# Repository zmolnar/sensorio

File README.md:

# The story of sensorio: a "smart" variometer

Since I left the university, I always wanted to gain a deeper understanding of how Kalman filters work in practice. I started to do research on the topic, until I found an excellent paper from [Roger Labbe](https://github.com/rlabbe/Kalman-and-Bayesian-Filters-in-Python), describing the Bayesian filters in great detail and in a very practical way.

After reading the book, I wanted to implement it in a real-life project. Since I'm a passionate paraglider pilot, building a variometer was a straightforward direction for me.

A variometer is a flight instrument, measuring vertical height and velocity, based on barometric pressure. Since pressure measurement is very noisy, in most cases (even in commercial products), a low pass filter is used to smoothen it, resulting in many seconds of lag in the output. This is how it has always been and this is something that every pilot has to learn how to compensate mentally, using prior experience and listening to other sources of information, like feeling of acceleration. It can be very hard to learn and master especially for beginners. To solve this, many people have already built variometers combining a pressure sensor and an accelerometer, with promising results.

I started to design the hardware, but I hit walls right at the beginning. The STM32 micros, that I have a lot of experience with, are not available due to global chip shortage, so I had to find an alternative. I choose ESP32, because it has lots of computing power, it is on stock and has additional built-in capabilities - like Bluetooth and WiFi - providing great potential for future developments.

The other crucial part of the project was to find the appropriate display. The special flying conditions require very good readability under any circumstances, therefore I choose the [LS027B7DH01](https://www.sharpsde.com/products/displays/model/ls027b7dh01/), a transflective LCD from Sharp, which I ordered from [Digikey](https://www.digikey.com/en/products/detail/sharp-microelectronics/LS027B7DH01/5054066).

I used KiCad for PCB design and FreeCAD for the housing. You can find the project files in the hardware and housing folders.

While waiting for the PCB, I started to experiment with Arduino, but I had to realize quickly that it is not suitable for me. I changed to ESP IDF and it was a very good decision. I am satisfied with the framework, it has lots of documentation, clear examples, a well designed interface, and works out of the box.

My first task was to fire up the sensors on the board, still using development kits:
+ [MS5611](https://www.amsys-sensor.com/products/pressure-sensor/ms5611-high-resolution-barometric-sensor-10-1200-mbar/) pressure sensor: I know this sensor very well, it was an easy task to make it work. I connected it to the ESP32 using I2C
+ [LS027B7DH01](https://www.sharpsde.com/products/displays/model/ls027b7dh01/): I used SPI to connect it to the MCU. I use the LVGL graphics library to implement the UI
+ [BNO055](https://www.bosch-sensortec.com/products/smart-sensors/bno055/) IMU from Bosch, who provides the needed driver too

The MS5611 and the LCD were very easy, but I struggled with the IMU. Everything worked fine for some time, but after a few seconds or sometimes minutes, the communication stopped and only a power reset could solve the problem. A friend of mine lent me a [Saleae](https://www.saleae.com/) Logic Pro 16, to investigate the issue, and I quickly found the root cause: the I2C clock stretching is not handled properly in the driver. After I added a timeout to mimic clock stretching, the issue disappeared and now the IMU works perfectly. The main issue was that BNO055 has a complex internal algorithm that takes some time to run, therefore it stretches the clock cycle until it finishes the task. The communication worked as long as the internal sensors were not ready, but after it had calibrated the system and started the algorithm, the communication stopped. I could have struggled a lot without a logic analyzer, because working with hardware without having a logic analyzer at hand is like solving a rubik's cube in a dark room without any visual feedback. Until each bit is in its exact position at the right time, the program does not work and it is very hard to find the root cause just by reading the code.
I was amazed by the build quality of the Saleae device. It is very simple to use, although I found it annoying that the labels numbering the input channels are placed on the backplane of the housing. Other than that, it is clearly a professional tool made for heavy duty embedded development. The software is simple to install and straightforward to use even without reading the manual, because it is really intuitive. I also experimented with an SD card and Saleae logic analyzer to discover the potential of the device. It looks really cool!

SD card setup

Wiring

Decoded SPI frame

Decoded SPI byte

400kHz SPI clock signal

After making the board up and running, I sampled input data using real sensors, and started to experiment with Kalman filters. First, I designed an unscented kalman filter (UKF) using filterpy. I was truly satisfied by the results and started to work on my own implementation in C++.

Although the results were very promising at first sight, I encountered problems. I had to realize that the IMU has an orientation-dependent, constantly changing offset that introduces an unacceptable error in the final result. This offset is accumulated only in a standstill position and is eliminated internally when the device is moving, but it’s a bit annoying while waiting for take off.

The other, show stopper issue is that BNO055 is not suitable for this task. Since only the vertical acceleration is relevant for the computation, detecting the direction of the gravity vector is a crucial step. BNO055 fails to detect the vertical direction if the device is in a constantly accelerating situation and it provides false results. This happens when flying in a narrow thermal, resulting in a constantly beeping variometer indicating crazy climb rates, even though the vertical speed is minimal. This is totally unacceptable and I’m very disappointed. I didn’t recognize this problem early enough when selecting the accelerometer, although even the documentation does not emphasise it either. Only a small note states this behavior, which is very frustrating. Lessons learned ...

Considering the results, I decided to build a new device using 4 baro sensors and no IMU. This way I can increase the sampling rate and make the device more responsive to changes without the problems introduced by accelerometers. I could also try [Madgwick's](https://x-io.co.uk/open-source-imu-and-ahrs-algorithms/) algorithm, but I decided to go in this direction first.

This project is still in concept phase, it requires a lot of work to finish it. Until then watch these videos and stay tuned!

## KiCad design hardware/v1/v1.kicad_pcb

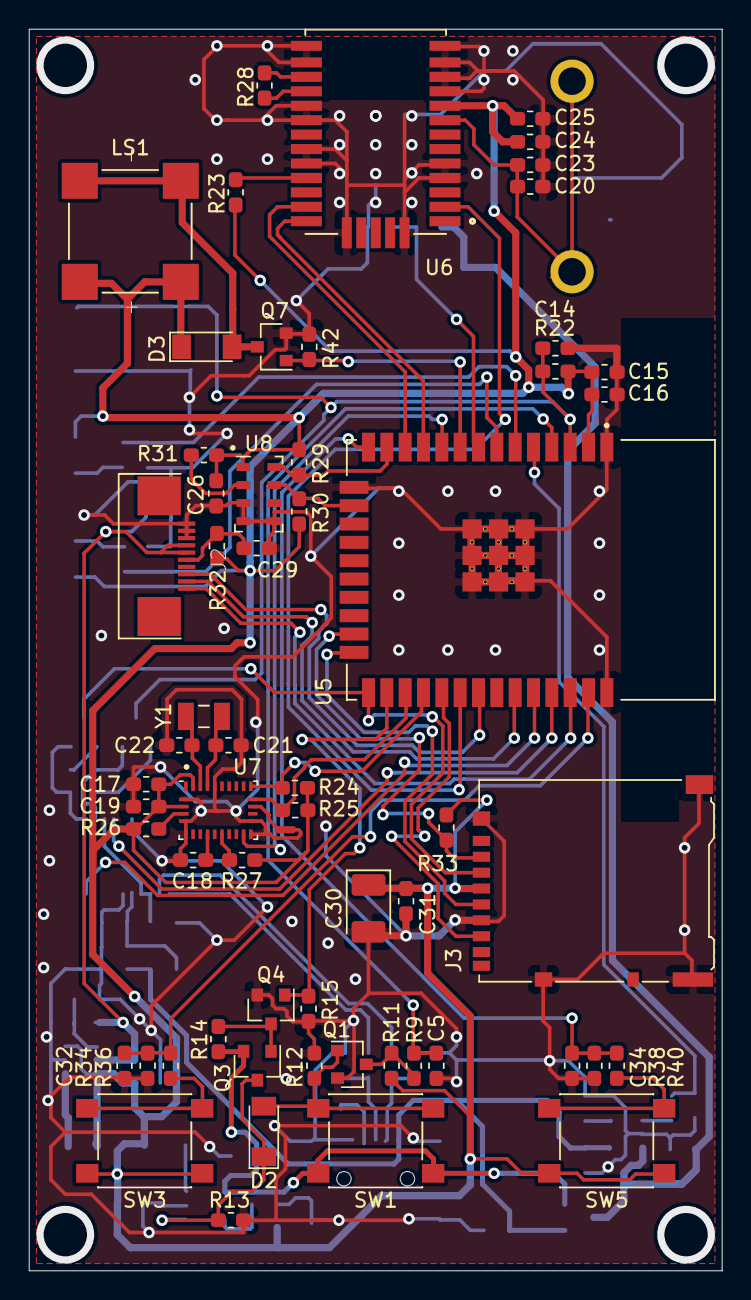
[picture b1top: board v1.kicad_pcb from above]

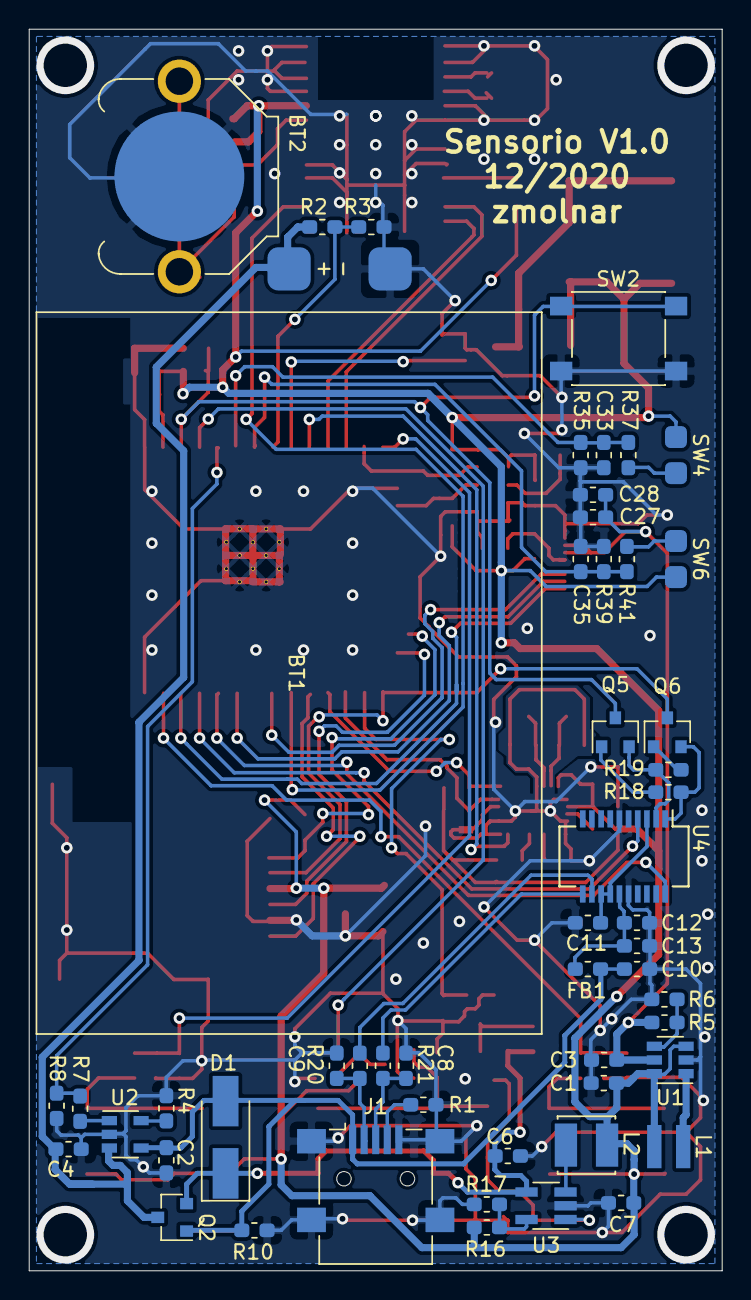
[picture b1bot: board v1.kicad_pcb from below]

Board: 2 copper layers, 48.0 x 86.0 mm, 112 parts (52 on the bottom side), 71 nets.

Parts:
BT1: Li-Po, 3,7V; Battery_103450
BT2: CR1220; BatteryHolder_Keystone_3001_1x12mm
C1, C23: 4u7; C_0603_1608Metric_Pad1.05x0.95mm_HandSolder
C2, C4, C6, C13: 4.7u; C_0603_1608Metric_Pad1.05x0.95mm_HandSolder
C3, C7, C24: 10u; C_0603_1608Metric_Pad1.05x0.95mm_HandSolder
C5, C32, C33, C34, C35: 10n; C_0603_1608Metric_Pad1.05x0.95mm_HandSolder
C8, C9: 47p; C_0603_1608Metric_Pad1.05x0.95mm_HandSolder
C10, C11, C12, C14, C16, C19, C20, C25, C26, C29, C31: 100n; C_0603_1608Metric_Pad1.05x0.95mm_HandSolder
C15: 22u; C_0603_1608Metric_Pad1.05x0.95mm_HandSolder
C17: 150n; C_0603_1608Metric_Pad1.05x0.95mm_HandSolder
C18, C27, C28: 1u; C_0603_1608Metric_Pad1.05x0.95mm_HandSolder
C21, C22: 12p; C_0603_1608Metric_Pad1.05x0.95mm_HandSolder
C30: 47u; CP_EIA-3528-21_Kemet-B_Pad1.50x2.35mm_HandSolder
D1: SK24A; D_SMA_Handsoldering
D2, D3: LL46; D_MiniMELF
FB1: Ferrite_Bead; L_0603_1608Metric_Pad1.05x0.95mm_HandSolder
J1: USB_B_Mini; USB_Mini-B_Lumberg_2486_01_Horizontal
J2: Conn_01x10; Wuerth_10pin_FPC_68711014022
J3: Micro_SD_Card_Det; microSD_HC_Hirose_DM3AT-SF-PEJM5
L1: 4u7; Viking_Tech_SDIA0315
L2: 2.2uH; Murata_2u2H_LQH44PN2R2MP0L
LS1: KSSGJ4D20
NT1: GND-to-COM2; NetTie-2_SMD_Pad0.5mm
Q1, Q4, Q7: 2N7002; SOT-23
Q2: DMG2301L; SOT-23
Q3: FDV304P; SOT-23
Q5, Q6: BC817; SOT-23
R1, R10, R11, R12, R13, R14, R15: 100k; R_0603_1608Metric_Pad1.05x0.95mm_HandSolder
R2, R6, R8: 220k; R_0603_1608Metric_Pad1.05x0.95mm_HandSolder
R3, R5: 680k; R_0603_1608Metric_Pad1.05x0.95mm_HandSolder
R4: 2k; R_0603_1608Metric_Pad1.05x0.95mm_HandSolder
R7: 110k; R_0603_1608Metric_Pad1.05x0.95mm_HandSolder
R9, R36, R37, R40, R41: 1k; R_0603_1608Metric_Pad1.05x0.95mm_HandSolder
R16: 680; R_0603_1608Metric_Pad1.05x0.95mm_HandSolder
R17: 150; R_0603_1608Metric_Pad1.05x0.95mm_HandSolder
R18, R19, R22, R23, R24, R25, R26, R27, R29, R30, R31, R32, R33, R34, R35, R38, R39: 10k; R_0603_1608Metric_Pad1.05x0.95mm_HandSolder
R20, R21: 27R; R_0603_1608Metric_Pad1.05x0.95mm_HandSolder
R28: 0R; R_0603_1608Metric_Pad1.05x0.95mm_HandSolder
R42: 100K; R_0603_1608Metric_Pad1.05x0.95mm_HandSolder
SW1: BT0; SW_SPST_PTS645
SW2: RESET; SW_SPST_PTS645
SW3: BT1; SW_SPST_PTS645
SW4: BT3; Connector_SMD_01x02_2.54
SW5: BT2; SW_SPST_PTS645
SW6: BT4; Connector_SMD_01x02_2.54
U1: MCP1640CH; SOT-23-6
U2: MCP73831-2-OT; SOT-23-5
U3: TLV62565; SOT-23-5_HandSoldering
U4: FT231XS; SSOP-20_3.9x8.7mm_P0.635mm
U5: ESP32-WROOM-32D
U6: Quectel_L96-M33
U7: BNO055; LGA-28_5.2x3.8mm_P0.5mm
U8: MS5611-01BA; LGA-8_3x5mm_P1.25mm
Y1: Crystal; Abracon_ABS07-32.768KHZ-T

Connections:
+3V3: C1.1, C7.1, C15.1, C16.1, C17.2, C19.2, C24.1, C25.1, C26.2, C30.1, C31.1, D3.1, J3.4, L1.1, L2.2, LS1.P1, LS1.P2, R11.1, R16.1, R22.1, R23.1, R24.1, R25.1, R26.1, R27.1, R29.1, R30.1, R31.1, R32.1, R33.1, SW3.2, SW4.2, SW5.2, SW6.2, U1.3, U1.6, U5.2, U6.9, U7.3, U7.28, U8.1
+5V: C3.1, C27.1, C28.1, J2.6, J2.7, R5.1, U1.5
+BATT: BT1.1, C4.1, Q2.3, R2.1, U2.3
BAT-ADC: R2.2, R3.1, U5.8
BAT-STAT: R7.2, R8.1, U5.5
BMP-SCL: R29.2, U5.13, U8.8
BMP-SDA: R30.2, U5.16, U8.7
BNO-INT: U5.10, U7.14
BNO-SCL: R25.2, U5.27, U7.19
BNO-SDA: R24.2, U5.28, U7.20
BT1: C32.1, R34.1, R36.2, U5.37
BT2: C34.1, R38.1, R40.2, U5.14
BT3: C33.1, R35.1, R37.2, U5.6
BT4: C35.1, R39.1, R41.2, U5.7
BUZZER: Q7.1, R42.1, U5.9
DTR: Q6.2, R18.2, U4.1
ESP32-EN: C14.1, Q5.3, R22.2, SW2.2, U5.3
ESP32-IO0: J3.3, Q6.3, U5.25
ESP32-RXD0: U4.20, U5.34
ESP32-TXD0: U4.4, U5.35
GND: BT1.2, BT2.2, C1.2, C2.2, C3.2, C4.2, C5.2, C6.2, C7.2, C8.2, C9.2, C10.2, C11.2, C12.2, C13.2, C14.2, C15.2, C16.2, C17.1, C18.2, C19.1, C20.2, C21.1, C22.1, C23.2, C24.2, C25.2, C26.1, C27.2, C28.2, C29.2, C30.2, C31.2, C32.2, C33.2, C34.2, C35.2, J1.5, J1.6, J2.8, J2.9, J2.10, J3.6, J3.11, NT1.2, Q1.2, Q4.2, Q7.2, R1.2, R3.2, R4.2, R6.2, R8.2, R10.2, R12.2, R13.2, R15.2, R17.2, R34.2, R35.2, R38.2, R39.2, R42.2, SW2.1, U1.2, U2.2, U3.2, U4.6, U4.16, U5.1, U5.15, U5.38, U5.39_1, U5.39_2, U5.39_3, U5.39_4, U5.39_5, U5.39_6, U5.39_7, U5.39_8, U5.39_9, U5.39_10, U5.39_11, U5.39_12, U5.39_13, U5.39_14, U5.39_15, U5.39_16, U5.39_17, U5.39_18, U5.39_19, U5.39_20, U5.39_21, U6.4, U6.5, U6.10, U6.11, U6.12, U6.13, U6.14, U6.15, U6.18, U6.19, U6.21, U6.22, U6.27, U6.31, U7.2, U7.5, U7.6, U7.15, U7.16, U7.25, U8.3, U8.4, U8.5
GPS-3DFIX: U5.30, U6.2
GPS-RX: U5.11, U6.26
GPS-TX: U5.12, U6.25
LCD-CS: J2.3, U5.31
LCD-MOSI: J2.2, U5.33
LCD-SCLK: J2.1, U5.36
unnamed: BT2.1, C20.1, C23.1, U6.8
unnamed: C11.1, U4.3, U4.13, U4.14
unnamed: C12.1, C13.1, FB1.1, U4.15
unnamed: C18.1, U7.9
unnamed: C21.2, U7.26, Y1.1
unnamed: C22.2, U7.27, Y1.2
unnamed: C29.1, J2.5, R32.2
unnamed: D2.2, Q1.1, R12.1, SW1.1
unnamed: D3.2, LS1.N1, LS1.N2, Q7.3
unnamed: J1.4, R1.1
unnamed: L1.2, U1.1
unnamed: L2.1, U3.3
unnamed: NT1.1, U7.18
unnamed: Q1.3, R9.1, R11.2
unnamed: Q3.1, Q4.3, R14.2
unnamed: Q5.1, R18.1
unnamed: Q6.1, R19.1
unnamed: R4.1, U2.5
unnamed: R5.2, R6.1, U1.4
unnamed: R7.1, U2.1
unnamed: R16.2, R17.1, U3.5
unnamed: R20.1, U4.12
unnamed: R21.1, U4.11
unnamed: R23.2, U6.23
unnamed: R26.2, U7.4
unnamed: R27.2, U7.11
unnamed: R28.1, U6.16
unnamed: R28.2, U6.17
unnamed: R31.2, U8.2
unnamed: R36.1, SW3.1
unnamed: R37.1, SW4.1
unnamed: R40.1, SW5.1
unnamed: R41.1, SW6.1
POW-EN: Q4.1, R15.1, U5.26
RTS: Q5.2, R19.2, U4.2
SDC-CS: J3.2, R33.2, U5.23
SDC-MISO: J3.7, U5.29
SDC-SCK: J3.5, U5.24
TLV62565-EN: D2.1, Q3.3, R13.1, U3.1
TLV62656-VIN: C6.1, D1.1, Q2.2, Q3.2, R14.1, SW1.2, U3.4
USB-DM: C9.1, J1.2, R20.2
USB-DP: C8.1, J1.3, R21.2
USB-VCC: C2.1, C10.1, D1.2, FB1.2, J1.1, Q2.1, R10.1, U2.4
nBT0: C5.1, R9.2, U5.4

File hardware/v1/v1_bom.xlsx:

Id | Designator | Package | Quantity | Designation | Supplier and ref
1 | BT1 | Battery_103450 | 1 | Li-Po, 3,7V
2 | BT2 | BatteryHolder_Keystone_3001_1x12mm | 1 | CR1220
3 | R42 | R_0603_1608Metric_Pad1.05x0.95mm_HandSolder | 1 | 100K
4 | J2 | Wuerth_10pin_FPC_68711014022 | 1 | Conn_01x10
5 | SW6 | Connector_SMD_01x02_2.54 | 1 | BT4
6 | SW4 | Connector_SMD_01x02_2.54 | 1 | BT3
7 | Y1 | Abracon_ABS07-32.768KHZ-T | 1 | Crystal
8 | U8 | LGA-8_3x5mm_P1.25mm | 1 | MS5611-01BA
9 | U7 | LGA-28_5.2x3.8mm_P0.5mm | 1 | BNO055
10 | U6 | Quectel_L96-M33 | 1 | Quectel_L96-M33
11 | U5 | ESP32-WROOM-32D | 1 | ESP32-WROOM-32D
12 | U4 | SSOP-20_3.9x8.7mm_P0.635mm | 1 | FT231XS
13 | U3 | SOT-23-5_HandSoldering | 1 | TLV62565
14 | U2 | SOT-23-5 | 1 | MCP73831-2-OT
15 | U1 | SOT-23-6 | 1 | MCP1640CH
16 | SW5 | SW_SPST_PTS645 | 1 | BT2
17 | SW3 | SW_SPST_PTS645 | 1 | BT1
18 | SW2 | SW_SPST_PTS645 | 1 | RESET
19 | SW1 | SW_SPST_PTS645 | 1 | BT0
20 | R41,R40,R37,R36,R9 | R_0603_1608Metric_Pad1.05x0.95mm_HandSolder | 5 | 1k
21 | R39,R38,R35,R34,R33,R32,R31,R30,R29,R27,R26,R25,R24,R23,R22,R19,R18 | R_0603_1608Metric_Pad1.05x0.95mm_HandSolder | 17 | 10k
22 | R28 | R_0603_1608Metric_Pad1.05x0.95mm_HandSolder | 1 | 0R
23 | R21,R20 | R_0603_1608Metric_Pad1.05x0.95mm_HandSolder | 2 | 27R
24 | R17 | R_0603_1608Metric_Pad1.05x0.95mm_HandSolder | 1 | 150
25 | R16 | R_0603_1608Metric_Pad1.05x0.95mm_HandSolder | 1 | 680
26 | R15,R14,R13,R12,R11,R10,R1 | R_0603_1608Metric_Pad1.05x0.95mm_HandSolder | 7 | 100k
27 | R8,R6,R2 | R_0603_1608Metric_Pad1.05x0.95mm_HandSolder | 3 | 220k
28 | R7 | R_0603_1608Metric_Pad1.05x0.95mm_HandSolder | 1 | 110k
29 | R5,R3 | R_0603_1608Metric_Pad1.05x0.95mm_HandSolder | 2 | 680k
30 | R4 | R_0603_1608Metric_Pad1.05x0.95mm_HandSolder | 1 | 2k
31 | Q7,Q4,Q1 | SOT-23 | 3 | 2N7002
32 | Q6,Q5 | SOT-23 | 2 | BC817
33 | Q3 | SOT-23 | 1 | FDV304P
34 | Q2 | SOT-23 | 1 | DMG2301L
35 | NT1 | NetTie-2_SMD_Pad0.5mm | 1 | GND-to-COM2
36 | LS1 | KSSGJ4D20 | 1 | KSSGJ4D20
37 | L2 | Murata_2u2H_LQH44PN2R2MP0L | 1 | 2.2uH
38 | L1 | Viking_Tech_SDIA0315 | 1 | 4u7
39 | J3 | microSD_HC_Hirose_DM3AT-SF-PEJM5 | 1 | Micro_SD_Card_Det
40 | J1 | USB_Mini-B_Lumberg_2486_01_Horizontal | 1 | USB_B_Mini
41 | FB1 | L_0603_1608Metric_Pad1.05x0.95mm_HandSolder | 1 | Ferrite_Bead
42 | D3,D2 | D_MiniMELF | 2 | LL46
43 | D1 | D_SMA_Handsoldering | 1 | SK24A
44 | C35,C34,C33,C32,C5 | C_0603_1608Metric_Pad1.05x0.95mm_HandSolder | 5 | 10n
45 | C31,C29,C26,C25,C20,C19,C16,C14,C12,C11,C10 | C_0603_1608Metric_Pad1.05x0.95mm_HandSolder | 11 | 100n
46 | C30 | CP_EIA-3528-21_Kemet-B_Pad1.50x2.35mm_HandSolder | 1 | 47u
47 | C28,C27,C18 | C_0603_1608Metric_Pad1.05x0.95mm_HandSolder | 3 | 1u
48 | C24,C7,C3 | C_0603_1608Metric_Pad1.05x0.95mm_HandSolder | 3 | 10u
49 | C23,C1 | C_0603_1608Metric_Pad1.05x0.95mm_HandSolder | 2 | 4u7
50 | C22,C21 | C_0603_1608Metric_Pad1.05x0.95mm_HandSolder | 2 | 12p
51 | C17 | C_0603_1608Metric_Pad1.05x0.95mm_HandSolder | 1 | 150n
52 | C15 | C_0603_1608Metric_Pad1.05x0.95mm_HandSolder | 1 | 22u
53 | C13,C6,C4,C2 | C_0603_1608Metric_Pad1.05x0.95mm_HandSolder | 4 | 4.7u
54 | C9,C8 | C_0603_1608Metric_Pad1.05x0.95mm_HandSolder | 2 | 47p

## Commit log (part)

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2020-06-02 Add ChibiOS submodule.
2020-06-02 Add lvgl submodule.
2020-06-02 Copy files from stm32f103-stk EPD prototyping.
2020-06-02 Add .gitignore to build folder.
2020-06-02 Add project level .gitignore.
2020-06-02 Reformat paraglider image array.
2020-07-07 Reorganize folder structure.
2020-07-07 Update gitignore file.
2020-07-11 Copy demo from ChibiOS repo.
2020-07-12 Update board config files and add template for ChibiStudio.
2020-07-17 Create LED blinker and configure SWO pin.
2020-07-18 Add sampler thread ans LPS22HB sensor to the project.
2020-07-19 Add LPS22HB DRDY interrupt handling.
2020-07-19 Remove ChibiOS submodule and add its content as source files.
2020-09-19 Add SWO printout to debug data.
2020-10-14 Make UART work to transmit data. Setup LSM6DSL sensor.
2020-10-16 Fix issues.
2020-12-06 Board V1.0 all nets connected.
2020-12-06 Tracks sorted out, without ground plane.
2020-12-07 V1.0 RC1
2020-12-08 V1.0 RC2
2020-12-09 V1.0 RC3
2020-12-09 V1.0 final revision
2020-12-24 Remove all files from firmware folder.
2020-12-24 Initialize platformio project.
2020-12-25 Add MS5611 driver base with reset and PROM validation.
2020-12-26 Add temp and pressure conversion methods to the MS5611 driver.
2020-12-26 Add clang format configuration.
2020-12-26 Add official Bosch driver for the BNO055 IMU.
2020-12-27 Add cpp wrapper for the BST driver, and the IMU manager thread.
2020-12-27 Update MS5611 driver and thread.
2020-12-28 Add interrupt config support to the BNO055 driver.
2020-12-31 Add LVGL and Sharp memory LCD driver.
2020-12-31 Implement Encoder driver for LVGL.
2021-01-01 Add GPS manager thread.
2021-01-02 Add dashboard.
2021-01-02 Add EEPROM backup support for config in the dashboard.
2021-01-12 Fix bug in dashboard mutex lock/unlock.
2021-01-12 Make GPS manager thread work with real sensor.
2021-01-12 Write GPIO pin HIGH to keep the power enabled after startup.
2021-01-12 Simplify dashboard interface.
2021-01-12 Connect PressureReaderThread to the dashboard.
2021-01-14 Clean up IMU manager thread. Synchronization is still not fully implemented.
2021-01-14 Implement data sampling timer and task synchronization.
2021-01-14 Connect IMU manager thread to the dashboard.
2021-01-16 Make sharp memory LCD driver work with real hardware.
2021-01-17 Make the encoder driver work with real hardware.
2021-01-17 Restructure GUI source files.
2021-01-17 Add GUI simulator to the project.
2021-01-19 Add encoder to the simulator and implement exit confirmation before shutting down.
2021-01-19 Reorganize platformio config file.
2021-01-20 Fix mutual exclusion issue in handling of the shutdown request.
2021-01-20 Add Pressure Sensor screen to the gui.
2021-01-21 Add IMU data screen.
2021-01-22 Add Battery monitor thread to monitor the battery level.
2021-01-22 Implement charge status detection, although the voltage devider needs to be replaced with higher value resistors to make it work.
2021-01-22 Implement system statuc screen.
2021-01-22 Add GPS data screen.
2021-01-23 Add filter output to the dashboard.
2021-01-23 Implement USB present detection.
2021-01-23 Minor changes on the gui.
2021-01-23 Add hardware errata doc.
2021-01-24 Fix system status layout.
2021-01-24 Update BPS screen layout.
2021-01-24 Rename PressorSensorData files to BpsData.
2021-01-24 Update IMU data screen layout.
2021-01-24 Eliminate GPS data screen update delay when startup.
2021-01-24 Fix GPS data screen values.
2021-01-26 Update the variometer screen.
2021-01-27 Add housing to the project.
2021-01-27 Add cut for display cable to the housing front cover.
2021-01-28 Add openings for the buttons.
2021-01-28 Add screw holes and pads.
2021-01-30 Update bolt mounting.
2021-01-30 Add button.
2021-01-31 Add SD card and USB slots, and fix sizing.
2021-01-31 Add fillets to the front cover.
2021-01-31 Generate v0.1 meshes.
2021-02-11 Update dimensions to reflect printer tolerance.
2021-02-11 Add v0.2 meshes.
2021-02-11 Update dimensions to 0.4mm tolerance.
2021-02-11 Add air intake.
2021-02-11 Add v0.3 meshes.
2021-02-12 Fix encoder group manipulation when exit is cancelled.
2021-02-15 Increase display frame thickness.
2021-02-15 Add v0.4 meshes.
2021-02-16 Modify screen update strategy and extend the dashboard with config parameters.
2021-02-18 Implement vario settings screen and fix config handling.
2021-02-22 Create back cover.
2021-03-09 Implement data filter thread and add python model for the Kalman filter.
2021-03-09 Add vscode folder to gitignore.
2021-03-20 Implement matrix class and PC simulator for modeling UKF.
2021-03-26 Backup commit, needs more work and heavy refactoring.
2021-03-26 Rename env folder to src.
2021-03-26 Add googletest to the project.
2021-03-27 Add tests for Matrix class and fix bugs.
2021-03-27 Add tests and fix bugs.
2021-03-27 Rename files.
2021-03-27 Implement matrix equality operator.
2021-03-27 Add test for MerweScaledSigmaPoints class.
2021-03-28 Add test for Ukf.
2021-03-30 Cut out unscented transformatioin and create a new function.
2021-03-30 Implement UKF::update and add tests too.
2021-03-31 Fix platformio compiler issues.
2021-03-31 Add calibration status to the IMU screen.
2021-03-31 Add UKF to the data filter thread.
2021-03-31 Add input parameters to main.
2021-03-31 Add command line parameters to the script.
2021-03-31 Improve kalmanfilter script.
2021-04-03 First promising results. Need to clean it up.
2021-04-03 Split out datfile parsing.
2021-04-03 Create a function for data processing.
2021-04-03 Run the filter with different parameters to compare the results.
2021-04-03 Add labels for plots.
2021-04-11 Fix GPS data display.
2021-04-12 Use linear acceleration calculated by BNO055.
2021-04-12 Add IMU calibration to the dashboard. Refactor needed.
2021-04-15 Implement IMU calibration.
2021-04-16 Modify variometer screen.
2021-04-16 Update indexes in script.
2021-04-16 Add QNH setting to the gui.
2021-04-16 Add filter parameters structure to the dashboard.
2021-04-20 Change QNH parameter to be a double.
2021-04-20 Add thread for logging data.
2021-04-24 Implement SD card data logging.
2021-04-24 Use semaphore instead of notification to sync data filtering thread.
2021-04-24 Use binary semaphore to sync IMU manager thread.
2021-04-29 Add beep control thread.
2021-04-29 Modify sensor init sequence for IMU and BPS.
2021-05-07 Add beep parameters to the config.
2021-05-07 Fix dt in sd card logging.
2021-05-08 Fix displaying speed on GPS data screen.
2021-05-10 Refactor IMU manager thread.
2021-05-10 Invert error logic in IMU manager. (Functions return true in case of error and false upon success.)
2021-05-17 Remove Arduino from the encoder, lcd and lvgl thread.
2021-05-18 Update config parameters.
2021-05-19 Make I2C and MS5611 work.
2021-05-22 Rebase BNO055 and Imu manager thread to use ESP IDF.
2021-05-23 Add EEPROM handling to config management.
2021-05-23 Add data filter thread.
2021-05-29 Add GPS Manager.
2021-05-29 Add battery monitor.
2021-05-30 Add data logger.
2021-05-31 Minor renaming and fixes.
2021-06-01 Fix the scheduling of sensor data sampling.
2021-06-05 Add local time handling and fix minor bugs.
2021-08-28 Fix GPS comm issue and prevent event storm.
2021-11-01 Fix ESP-IDF compilation bug by disabling MbedTLS Certificate Bundle.
2021-11-18 Rework Dashboard and Config modules.
2021-11-27 Rewrite kalman filtering using templates
2021-11-30 Set theme jekyll-theme-slate
2021-12-08 Rewrite logging related components.
2021-12-10 Rewrite Power module.
2021-12-10 Refactor battery monitor thread.
2021-12-10 Refactor data filter thread.
2021-12-10 Refactor data logger thread.
2021-12-10 Refactor GPS manager thread.
2021-12-10 Fix bug in Observer.
2021-12-12 Refactor pressure reader thread.
2022-02-12 Refactor beep control thread.
2022-02-12 Refactor encoder driver
2022-02-12 Refactor MS5611 driver
2022-02-12 Refactor LVGL thread
2022-02-12 Refacto LCD driver
2022-03-05 Update python model
2022-03-05 Make ETLCPP a submodule
2022-03-05 Implement NMEA parser
2022-03-05 Implement UKF without taking acceleration into account
2022-03-05 Add vscode file to gitignore
2022-03-05 Split Dashboard and Config into multiple files
2022-05-02 Convert LVGL from platformio dependency into a submodule
2022-06-30 Update readme file.
2022-07-30 Remove acceleration and use pressure only in calculations and add minor fixes
2022-07-30 Move hardware and housing design files into sensorio-hw repo.
2022-07-30 Fix data logger thread time handling.
